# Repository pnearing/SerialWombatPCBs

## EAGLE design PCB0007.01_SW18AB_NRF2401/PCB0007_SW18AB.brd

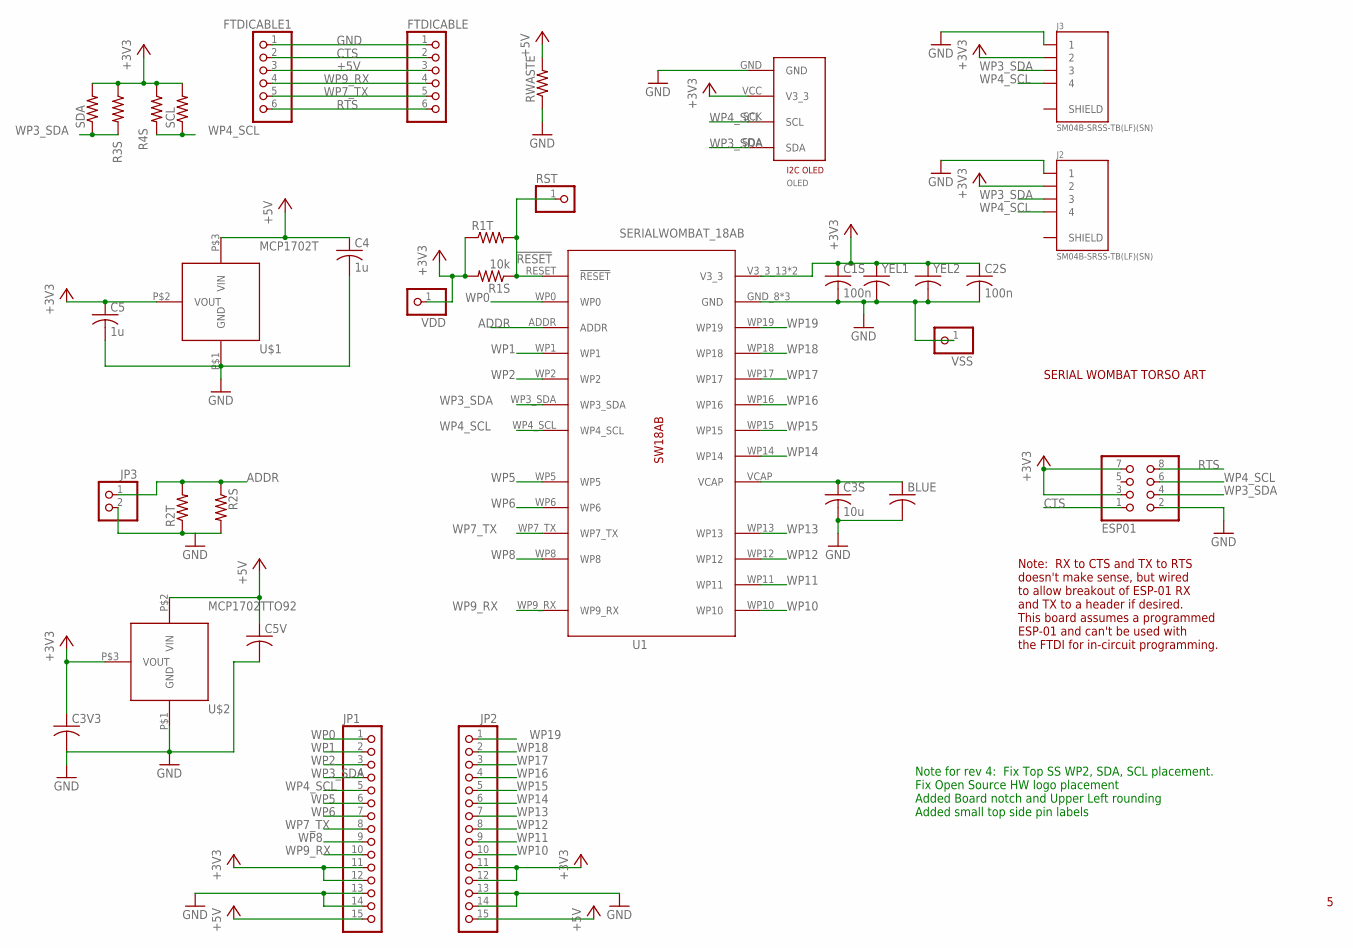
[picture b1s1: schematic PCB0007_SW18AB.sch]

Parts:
BLUE: C-US025-030X050; C025-030X050
C1S, C2S: 100n; C0603
C3S: 10u; C0805
C3V3, C5V: C-US025-030X050; C025-030X050
C4, C5: 1u; C0603
ESP01: PINHD-2X4; 2X04
FTDICABLE, FTDICABLE1: PINHD-1X6; 1X06
J2, J3: SM04B-SRSS-TB(LF)(SN); JST_SM04B-SRSS-TB(LF)(SN)
JP1, JP2: PINHD-1X15; 1X15
JP3: PINHD-1X2; 1X02
OLED: OLED_I2C; I2C_GND_VCC_SCL_SDA
R1S: 10k; R0603
R1T, R2T: R-US_0207/12; 0207/12
R2S, R3S, R4S: R-US_R0603; R0603
RST: PINHD-1X1; 1X01
RWASTE: R-US_R1206; R1206
SCL: R-US_0207/12; 0207/12
SDA: R-US_0207/12; 0207/12
U1: SERIALWOMBAT_18AB; SW18AB_DIP
U$1: MCP1702T; SOT_23A_MICROCHIP
U$2: MCP1702TTO92; TO-92
U$3: ART_SERIAL_WOMBAT_TORSO.33INHIGH; ART_SERIAL_WOMBAT_TORSO_THIRDINCH
VDD: PINHD-1X1; 1X01
VSS: PINHD-1X1; 1X01
YEL1, YEL2: C-US025-030X050; C025-030X050

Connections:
!RESET: R1S.1, R1T.2, RST.1, U1.RESET (!RESET)
+3V3: C1S.1, C2S.1, C3V3.1, C5.1, ESP01.3, ESP01.7, J2.2, J3.2, JP1.11, JP1.12, JP2.11, JP2.12, OLED.VCC (V3_3), R1S.2, R1T.1, R3S.1, R4S.1, SCL.2, SDA.2, U1.V3_3_13 (V3_3), U1.V3_3_28 (V3_3), U$1.P$2 (VOUT), U$2.P$3 (VOUT), VDD.1, YEL1.1, YEL2.1
+5V: C4.1, C5V.1, FTDICABLE.3, FTDICABLE1.3, JP1.15, JP2.15, RWASTE.2, U$1.P$3 (VIN), U$2.P$2 (VIN)
ADDR: JP3.1, R2S.1, R2T.2, U1.ADDR
CTS: ESP01.1, FTDICABLE.2, FTDICABLE1.2
GND: BLUE.2, C1S.2, C2S.2, C3S.2, C3V3.2, C4.2, C5.2, C5V.2, ESP01.2, FTDICABLE.1, FTDICABLE1.1, J2.1, J3.1, JP1.13, JP1.14, JP2.13, JP2.14, JP3.2, OLED.GND, R2S.2, R2T.1, RWASTE.1, U1.GND_8 (GND), U1.G_19 (GND), U1.G_27 (GND), U$1.P$1 (GND), U$2.P$1 (GND), VSS.1, YEL1.2, YEL2.2
unnamed: BLUE.1, C3S.1, U1.VCAP
RTS: ESP01.8, FTDICABLE.6, FTDICABLE1.6
WP0: JP1.1, U1.WP0
WP1: JP1.2, U1.WP1
WP2: JP1.3, U1.WP2
WP3_SDA: ESP01.4, J2.3, J3.3, JP1.4, OLED.SDA, R3S.2, SDA.1, U1.WP3_SDA
WP4_SCL: ESP01.6, J2.4, J3.4, JP1.5, OLED.SCK (SCL), R4S.2, SCL.1, U1.WP4_SCL
WP5: JP1.6, U1.WP5
WP6: JP1.7, U1.WP6
WP7_TX: FTDICABLE.5, FTDICABLE1.5, JP1.8, U1.WP7_TX
WP8: JP1.9, U1.WP8
WP9_RX: FTDICABLE.4, FTDICABLE1.4, JP1.10, U1.WP9_RX
WP10: JP2.10, U1.WP10
WP11: JP2.9, U1.WP11
WP12: JP2.8, U1.WP12
WP13: JP2.7, U1.WP13
WP14: JP2.6, U1.WP14
WP15: JP2.5, U1.WP15
WP16: JP2.4, U1.WP16
WP17: JP2.3, U1.WP17
WP18: JP2.2, U1.WP18
WP19: JP2.1, U1.WP19

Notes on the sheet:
Note: RX to CTS and TX to RTS doesn't make sense, but wired to allow breakout of ESP-01 RX and TX to a header if desired. This board assumes a programmed ESP-01 and can't be used with the FTDI for in-circuit programming.
Note for rev 4: Fix Top SS WP2, SDA, SCL placement. Fix Open Source HW logo placement Added Board notch and Upper Left rounding Added small top side pin labels

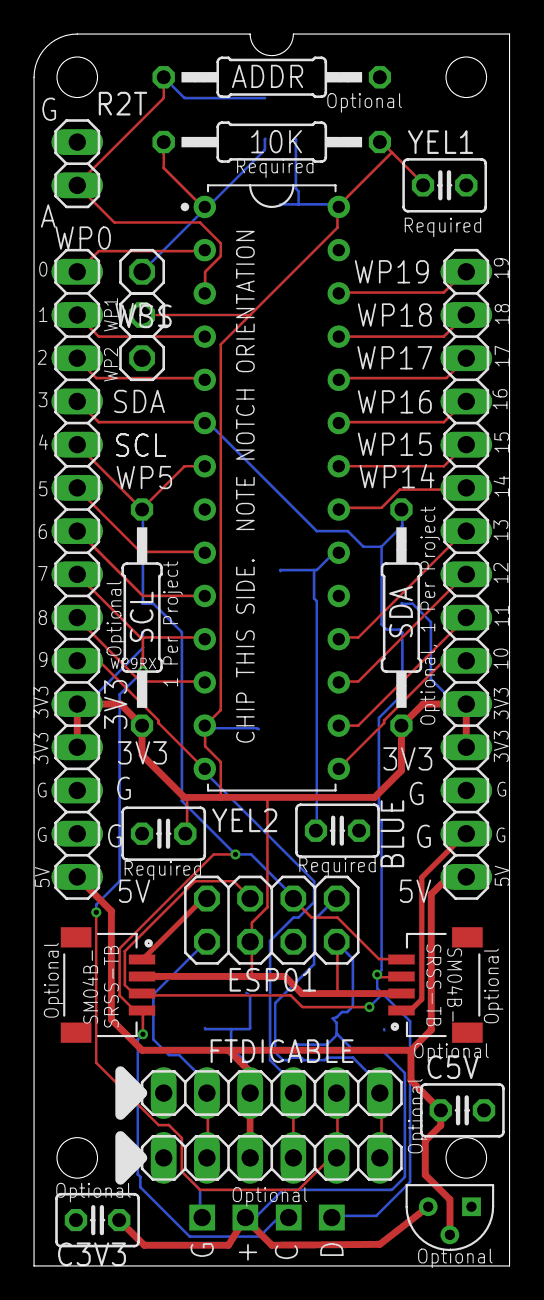
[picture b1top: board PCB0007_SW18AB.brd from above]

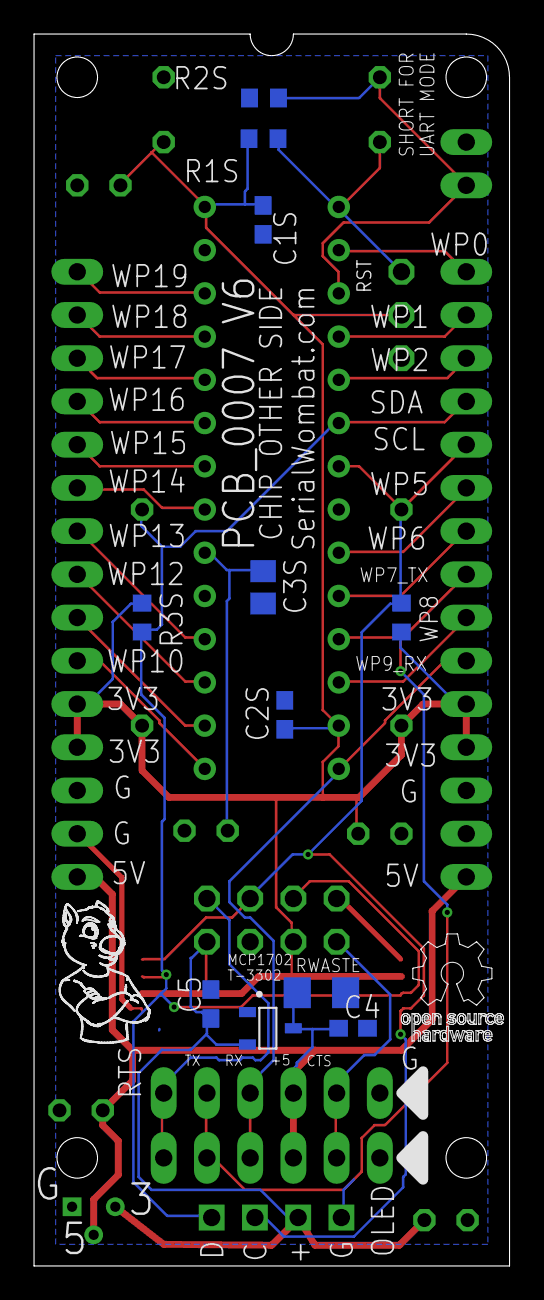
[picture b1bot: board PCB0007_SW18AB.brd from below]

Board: 2 copper layers, 27.9 x 72.4 mm, 35 parts (12 on the bottom side), 28 nets.

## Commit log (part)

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2025-06-26 Adding BUZZ Board V2 for OSHW certification
2025-06-26 Adding PCB0031 V2 for OSHW certification
2025-06-29 Adding SW8B Backpack V3 Hardware
2025-07-02 Uploading SW8B Bridge V3 for OSHWA certification
